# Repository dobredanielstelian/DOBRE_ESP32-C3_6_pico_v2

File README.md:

# DOBRE_ESP32-C3_6_pico_v2
ESP32-C3 evaluation board with e-ink display and multiple sensors

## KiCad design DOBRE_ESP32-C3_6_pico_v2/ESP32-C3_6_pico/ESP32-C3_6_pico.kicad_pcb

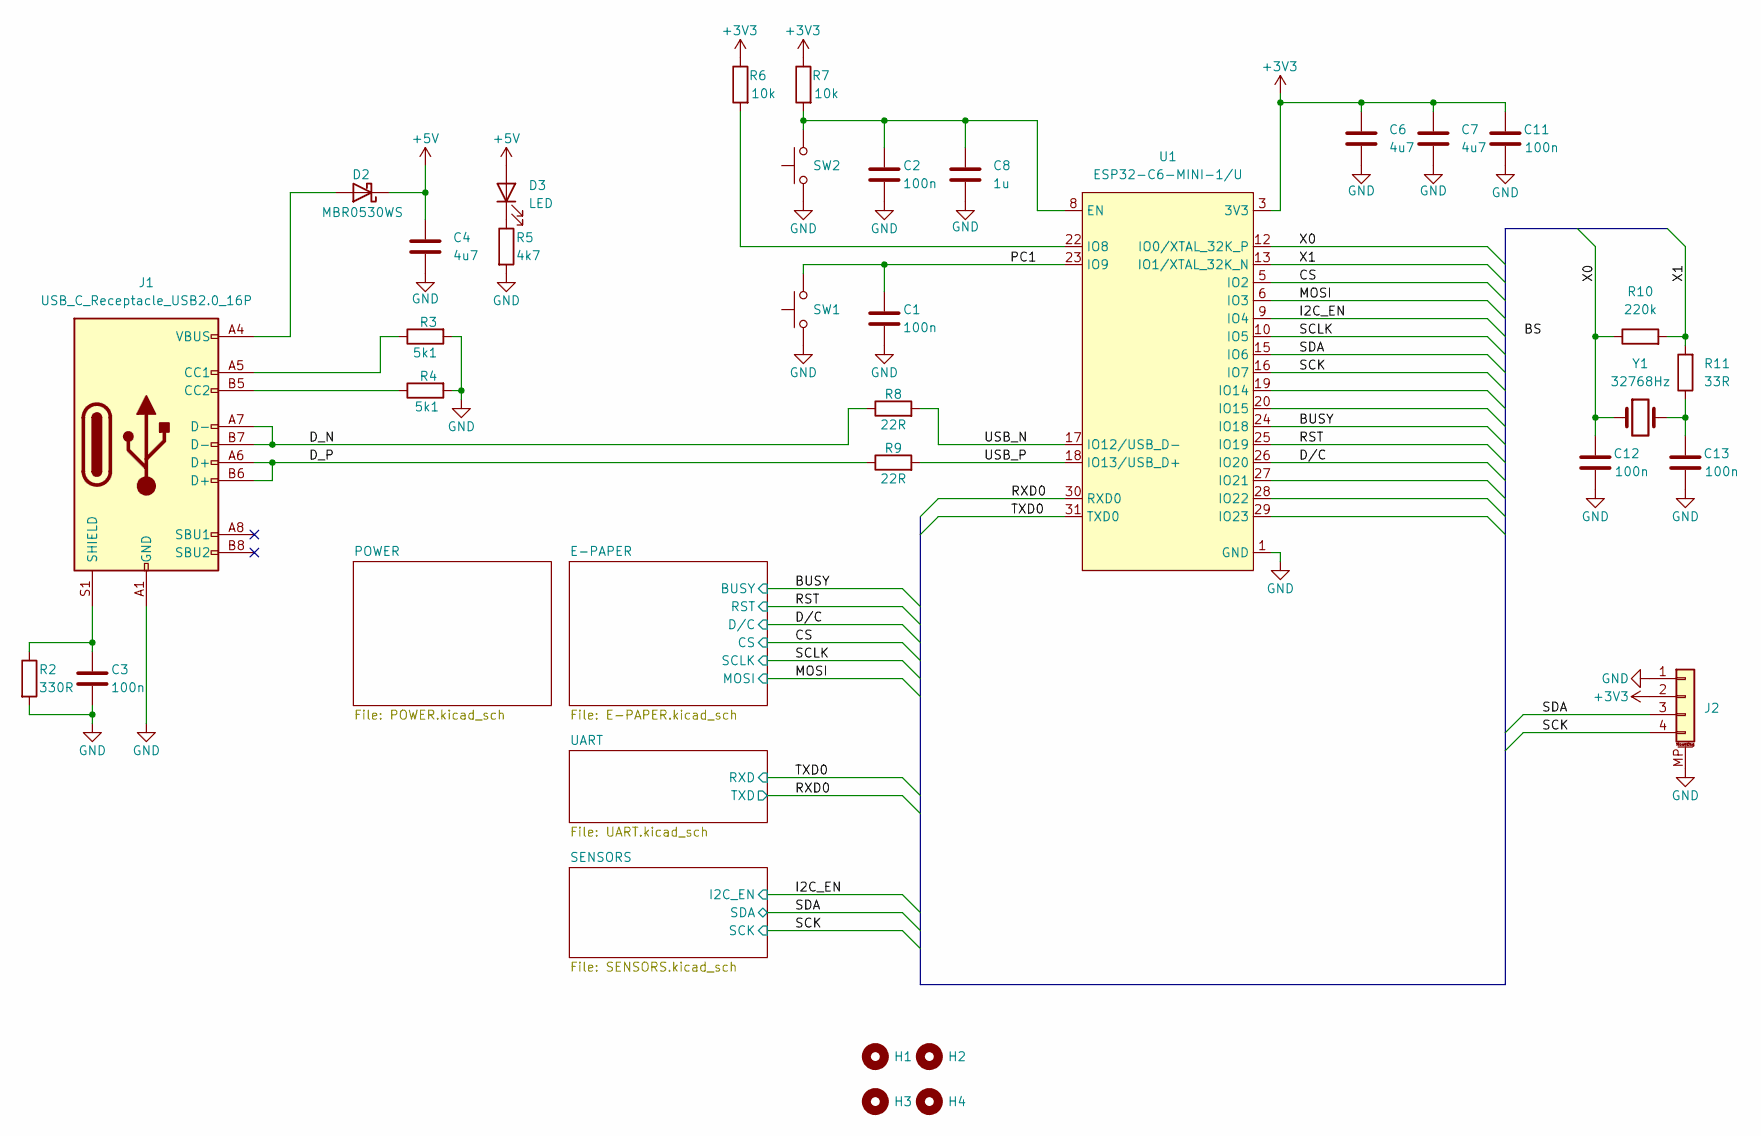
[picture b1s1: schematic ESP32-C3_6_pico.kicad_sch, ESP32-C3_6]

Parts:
C1, C2, C3, C11, C12, C13: 100n; C_0402_1005Metric
C4, C6, C7: 4u7; C_0402_1005Metric
C8: 1u; C_0402_1005Metric
D2: MBR0530WS; D_SOD-323
D3: LED; D_0402_1005Metric
H1, H2, H3, H4: MountingHole_3.2mm_M3
J1: USB_C_Receptacle_USB2.0_16P; USB_C_Receptacle_Palconn_UTC16-G
J2: Conn_01x04_MountingPin; JST_SH_SM04B-SRSS-TB_1x04-1MP_P1.00mm_Horizontal
R2: 330R; R_0402_1005Metric
R3, R4: 5k1; R_0402_1005Metric
R5: 4k7; R_0402_1005Metric
R6, R7: 10k; R_0402_1005Metric
R8, R9: 22R; R_0402_1005Metric
R10: 220k; R_0402_1005Metric
R11: 33R; R_0402_1005Metric
SW1, SW2: SW_Push; SW_Push_SPST_NO_Alps_SKRK
U1: ESP32-C6-MINI-1/U; ESP32-C6-MINI-1
Y1: 32768Hz; Crystal_SMD_2012-2Pin_2.0x1.2mm

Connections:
+3V3: C6.1, C7.1, C11.1, J2.2, R6.1, R7.1, U1.3 (3V3); also elsewhere on the board
+5V: C4.1, D2.1 (K), D3.2 (A); also elsewhere on the board
/BUSY: U1.24 (IO18); also elsewhere on the board
/CS: U1.5 (IO2); also elsewhere on the board
/D_N: J1.A7 (D-), J1.B7 (D-), R8.1
/D_P: J1.A6 (D+), J1.B6 (D+), R9.1
/D/C: U1.26 (IO20); also elsewhere on the board
/I2C_EN: U1.9 (IO4); also elsewhere on the board
/MOSI: U1.6 (IO3); also elsewhere on the board
/PC1: C1.1, SW1.2, U1.23 (IO9)
/RST: U1.25 (IO19); also elsewhere on the board
/RXD0: U1.30 (RXD0); also elsewhere on the board
/SCK: J2.4, U1.16 (IO7); also elsewhere on the board
/SCLK: U1.10 (IO5); also elsewhere on the board
/SDA: J2.3, U1.15 (IO6); also elsewhere on the board
/TXD0: U1.31 (TXD0); also elsewhere on the board
/USB_N: R8.2, U1.17 (IO12/USB_D-)
/USB_P: R9.2, U1.18 (IO13/USB_D+)
/X0: C12.1, R10.1, U1.12 (IO0/XTAL_32K_P), Y1.1
/X1: R10.2, R11.2, U1.13 (IO1/XTAL_32K_N)
GND: C1.2, C2.2, C3.2, C4.2, C6.2, C7.2, C8.2, C11.2, C12.2, C13.2, J1.A1 (GND), J1.A12 (GND), J1.B1 (GND), J1.B12 (GND), J2.1, J2.MP (MountPin), R2.2, R3.2, R4.2, R5.2, SW1.1, SW2.1, U1.1 (GND), U1.2 (GND), U1.11 (GND), U1.14 (GND), U1.36 (GND), U1.37 (GND), U1.38 (GND), U1.39 (GND), U1.40 (GND), U1.41 (GND), U1.42 (GND), U1.43 (GND), U1.44 (GND), U1.45 (GND), U1.46 (GND), U1.47 (GND), U1.48 (GND), U1.49 (GND), U1.50 (GND), U1.51 (GND), U1.52 (GND), U1.53 (GND); also elsewhere on the board
unnamed: C13.1, R11.1, Y1.2
unnamed: D2.2 (A), J1.A4 (VBUS), J1.A9 (VBUS), J1.B4 (VBUS), J1.B9 (VBUS)
unnamed: D3.1 (K), R5.1
unnamed: J1.A5 (CC1), R3.1
unnamed: J1.B5 (CC2), R4.1
unnamed: C3.1, J1.S1 (SHIELD), R2.1
unnamed: C2.1, C8.1, R7.2, SW2.2, U1.8 (EN)
unnamed: R6.2, U1.22 (IO8)
unnamed: U1.4 (NC), U1.7 (NC), U1.21 (NC), U1.32 (NC), U1.33 (NC), U1.34 (NC), U1.35 (NC)

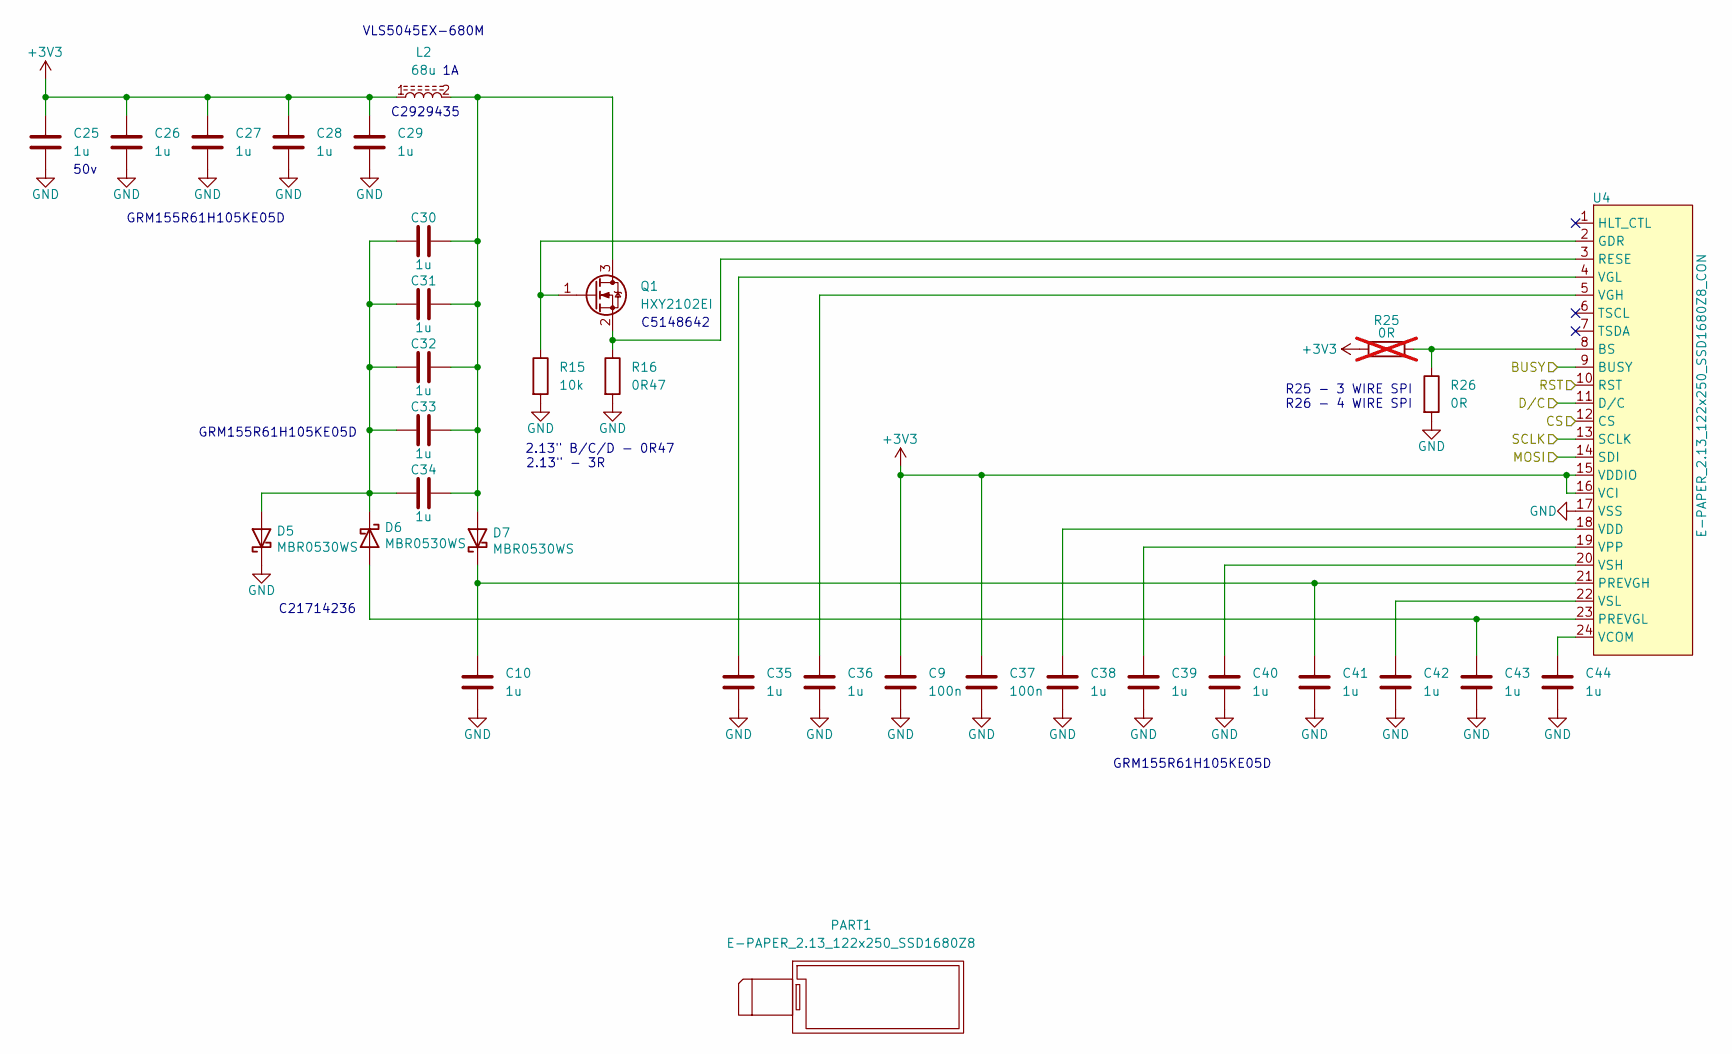
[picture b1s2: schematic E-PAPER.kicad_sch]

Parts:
C9, C37: 100n; C_0402_1005Metric
C10, C25, C26, C27, C28, C29, C30, C31, C32, C33, C34, C35, C36, C38, C39, C40, C41, C42, C43, C44: 1u; C_0402_1005Metric
D5, D6, D7: MBR0530WS; D_SOD-323
L2: 68u; Cx-54_inductor_C2929435
PART1: E-PAPER_2.13_122x250_SSD1680Z8
Q1: HXY2102EI; SOT-323_SC-70
R15: 10k; R_0402_1005Metric
R16: 0R47; R_0402_1005Metric
R25: 0R; R_0402_1005Metric; not fitted
R26: 0R; R_0402_1005Metric
U4: E-PAPER_2.13_122x250_SSD1680Z8_CON; TE_2-1734839-4_1x24-1MP_P0.5mm_Horizontal

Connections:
+3V3: C9.1, C25.1, C26.1, C27.1, C28.1, C29.1, C37.1, L2.1, R25.1, U4.15 (VDDIO), U4.16 (VCI); also elsewhere on the board
/BUSY: U4.9 (BUSY); also elsewhere on the board
/CS: U4.12 (CS); also elsewhere on the board
/D/C: U4.11 (D/C); also elsewhere on the board
/MOSI: U4.14 (SDI); also elsewhere on the board
/RST: U4.10 (RST); also elsewhere on the board
/SCLK: U4.13 (SCLK); also elsewhere on the board
GND: C9.2, C10.2, C25.2, C26.2, C27.2, C28.2, C29.2, C35.2, C36.2, C37.2, C38.2, C39.2, C40.2, C41.2, C42.2, C43.2, C44.2, D5.1 (K), R15.2, R16.2, R26.2, U4.17 (VSS), U4.MP; also elsewhere on the board
unnamed: C30.1, C31.1, C32.1, C33.1, C34.1, D5.2 (A), D6.1 (K)
unnamed: C43.1, D6.2 (A), U4.23 (PREVGL)
unnamed: C30.2, C31.2, C32.2, C33.2, C34.2, D7.2 (A), L2.2, Q1.3 (D)
unnamed: C10.1, C41.1, D7.1 (K), U4.21 (PREVGH)
unnamed: Q1.1 (G), R15.1, U4.2 (GDR)
unnamed: Q1.2 (S), R16.1, U4.3 (RESE)
unnamed: R25.2, R26.1, U4.8 (BS)
unnamed: C44.1, U4.24 (VCOM)
unnamed: C38.1, U4.18 (VDD)
unnamed: C36.1, U4.5 (VGH)
unnamed: C35.1, U4.4 (VGL)
unnamed: C39.1, U4.19 (VPP)
unnamed: C40.1, U4.20 (VSH)
unnamed: C42.1, U4.22 (VSL)

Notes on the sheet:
GRM155R61H105KE05D
C21714236
2.13" B/C/D - 0R47
C2929435
C5148642
R25 - 3 WIRE SPI R26 - 4 WIRE SPI
VLS5045EX-680M
50v
2.13" - 3R

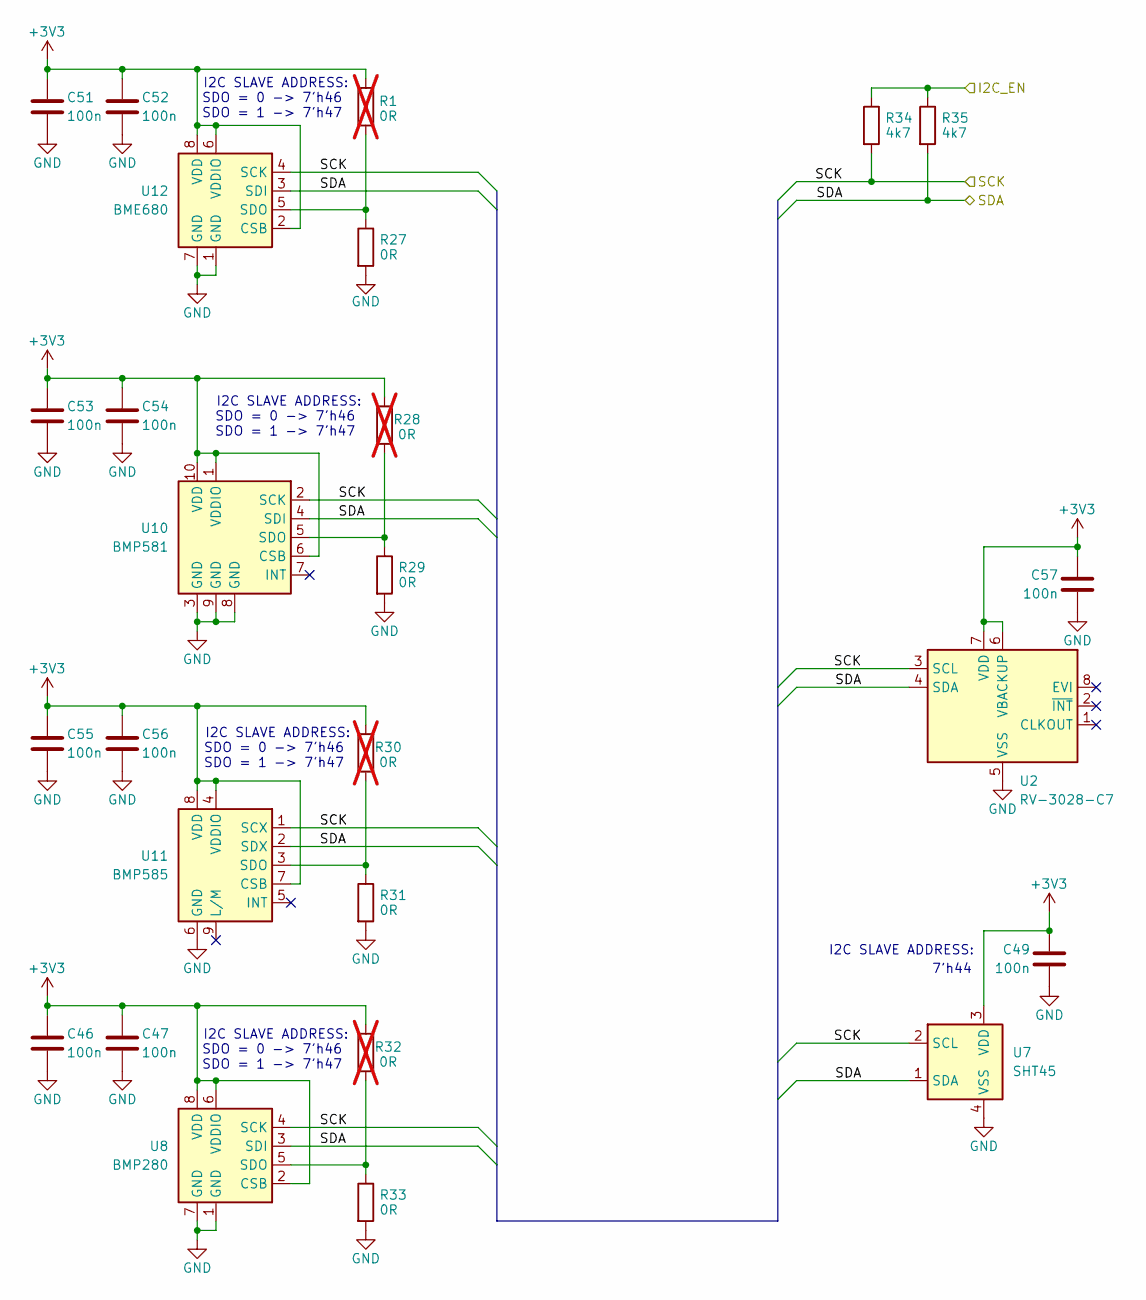
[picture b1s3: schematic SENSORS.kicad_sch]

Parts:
C46, C47, C49, C51, C52, C53, C54, C55, C56, C57: 100n; C_0402_1005Metric
R1, R28, R30, R32: 0R; R_0402_1005Metric; not fitted
R27, R29, R31, R33: 0R; R_0402_1005Metric
R34, R35: 4k7; R_0402_1005Metric
U2: RV-3028-C7
U7: SHT45; Sensirion_DFN-4_1.5x1.5mm_P0.8mm_SHT4x_NoCentralPad
U8: BMP280; Bosch_LGA-8_2x2.5mm_P0.65mm_ClockwisePinNumbering
U10: BMP581
U11: BMP585
U12: BME680; Bosch_LGA-8_3x3mm_P0.8mm_ClockwisePinNumbering

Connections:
+3V3: C46.1, C47.1, C49.1, C51.1, C52.1, C53.1, C54.1, C55.1, C56.1, C57.1, R1.2, R28.2, R30.2, R32.2, U2.6 (VBACKUP), U2.7 (VDD), U7.3 (VDD), U8.2 (CSB), U8.6 (VDDIO), U8.8 (VDD), U10.1 (VDDIO), U10.6 (CSB), U10.10 (VDD), U11.4 (VDDIO), U11.7 (CSB), U11.8 (VDD), U12.2 (CSB), U12.6 (VDDIO), U12.8 (VDD); also elsewhere on the board
/I2C_EN: R34.1, R35.1; also elsewhere on the board
/SCK: R34.2, U2.3 (SCL), U7.2 (SCL), U8.4 (SCK), U10.2 (SCK), U11.1 (SCX), U12.4 (SCK); also elsewhere on the board
/SDA: R35.2, U2.4 (SDA), U7.1 (SDA), U8.3 (SDI), U10.4 (SDI), U11.2 (SDX), U12.3 (SDI); also elsewhere on the board
GND: C46.2, C47.2, C49.2, C51.2, C52.2, C53.2, C54.2, C55.2, C56.2, C57.2, R27.2, R29.2, R31.2, R33.2, U2.5 (VSS), U7.4 (VSS), U8.1 (GND), U8.7 (GND), U10.3 (GND), U10.8 (GND), U10.9 (GND), U11.6 (GND), U12.1 (GND), U12.7 (GND); also elsewhere on the board
unnamed: R32.1, R33.1, U8.5 (SDO)
unnamed: R28.1, R29.1, U10.5 (SDO)
unnamed: R30.1, R31.1, U11.3 (SDO)
unnamed: R1.1, R27.1, U12.5 (SDO)

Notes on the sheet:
7'h44
SDO = 0 -> 7'h46 SDO = 1 -> 7'h47
I2C SLAVE ADDRESS:

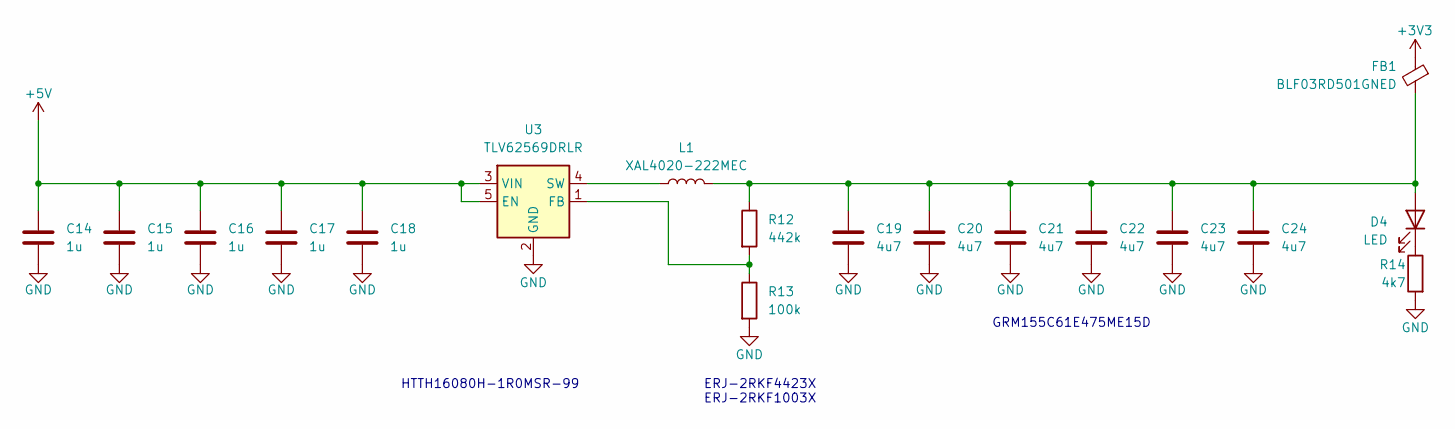
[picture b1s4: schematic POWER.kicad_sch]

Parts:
C14, C15, C16, C17, C18: 1u; C_0402_1005Metric
C19, C20, C21, C22, C23, C24: 4u7; C_0402_1005Metric
D4: LED; D_0402_1005Metric
FB1: BLF03RD501GNED; L_0402_1005Metric
L1: XAL4020-222MEC; L_Coilcraft_XxL4040
R12: 442k; R_0402_1005Metric
R13: 100k; R_0402_1005Metric
R14: 4k7; R_0402_1005Metric
U3: TLV62569DRLR; SOT-563

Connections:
+3V3: FB1.1; also elsewhere on the board
+5V: C14.1, C15.1, C16.1, C17.1, C18.1, U3.3 (VIN), U3.5 (EN); also elsewhere on the board
GND: C14.2, C15.2, C16.2, C17.2, C18.2, C19.2, C20.2, C21.2, C22.2, C23.2, C24.2, R13.2, R14.2, U3.2 (GND); also elsewhere on the board
unnamed: C19.1, C20.1, C21.1, C22.1, C23.1, C24.1, D4.2 (A), FB1.2, L1.2, R12.1
unnamed: D4.1 (K), R14.1
unnamed: R12.2, R13.1, U3.1 (FB)
unnamed: L1.1, U3.4 (SW)

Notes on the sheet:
GRM155C61E475ME15D
ERJ-2RKF4423X
ERJ-2RKF1003X
HTTH16080H-1R0MSR-99

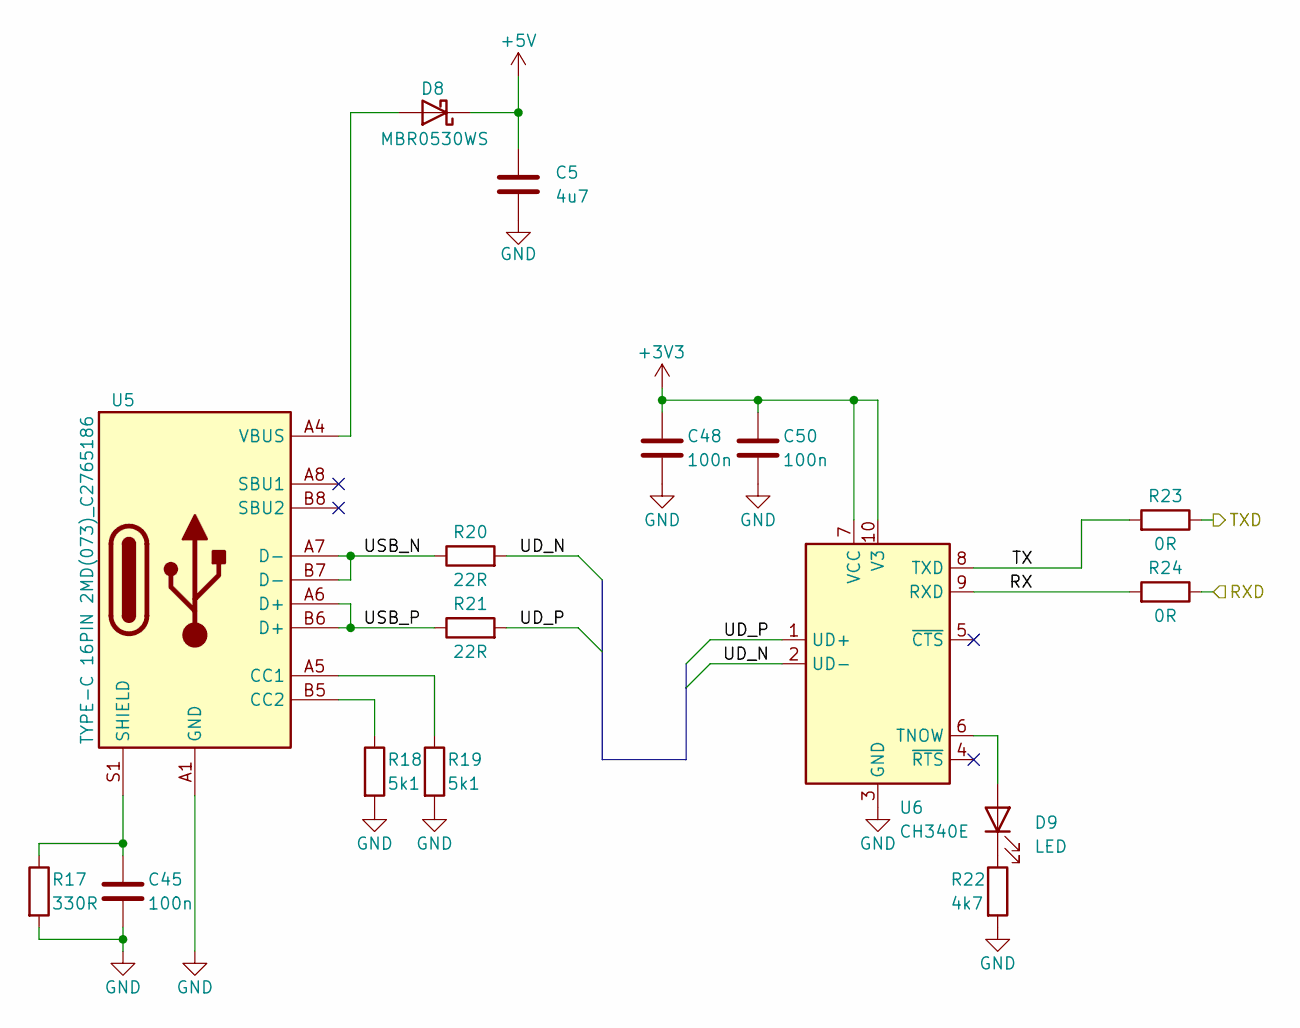
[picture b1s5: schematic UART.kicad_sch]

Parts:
C5: 4u7; C_0402_1005Metric
C45, C48, C50: 100n; C_0402_1005Metric
D8: MBR0530WS; D_SOD-323
D9: LED; D_0402_1005Metric
R17: 330R; R_0402_1005Metric
R18, R19: 5k1; R_0402_1005Metric
R20, R21: 22R; R_0402_1005Metric
R22: 4k7; R_0402_1005Metric
R23, R24: 0R; R_0402_1005Metric
U5: TYPE-C 16PIN 2MD(073)_C2765186; USB_C_Receptacle_Palconn_UTC16-G
U6: CH340E; MSOP-10_3x3mm_P0.5mm

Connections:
+3V3: C48.1, C50.1, U6.7 (VCC), U6.10 (V3); also elsewhere on the board
+5V: C5.1, D8.1 (K); also elsewhere on the board
/RXD0: R23.1; also elsewhere on the board
/TXD0: R24.1; also elsewhere on the board
/UART/RX: R24.2, U6.9 (RXD)
/UART/TX: R23.2, U6.8 (TXD)
/UART/UD_N: R20.2, U6.2 (UD-)
/UART/UD_P: R21.2, U6.1 (UD+)
/UART/USB_N: R20.1, U5.A7 (D-), U5.B7 (D-)
/UART/USB_P: R21.1, U5.A6 (D+), U5.B6 (D+)
GND: C5.2, C45.2, C48.2, C50.2, R17.2, R18.2, R19.2, R22.2, U5.A1 (GND), U5.A12 (GND), U5.B1 (GND), U5.B12 (GND), U6.3 (GND); also elsewhere on the board
unnamed: D8.2 (A), U5.A4 (VBUS), U5.A9 (VBUS), U5.B4 (VBUS), U5.B9 (VBUS)
unnamed: D9.2 (A), U6.6 (TNOW)
unnamed: D9.1 (K), R22.1
unnamed: R19.1, U5.A5 (CC1)
unnamed: R18.1, U5.B5 (CC2)
unnamed: C45.1, R17.1, U5.S1 (SHIELD)

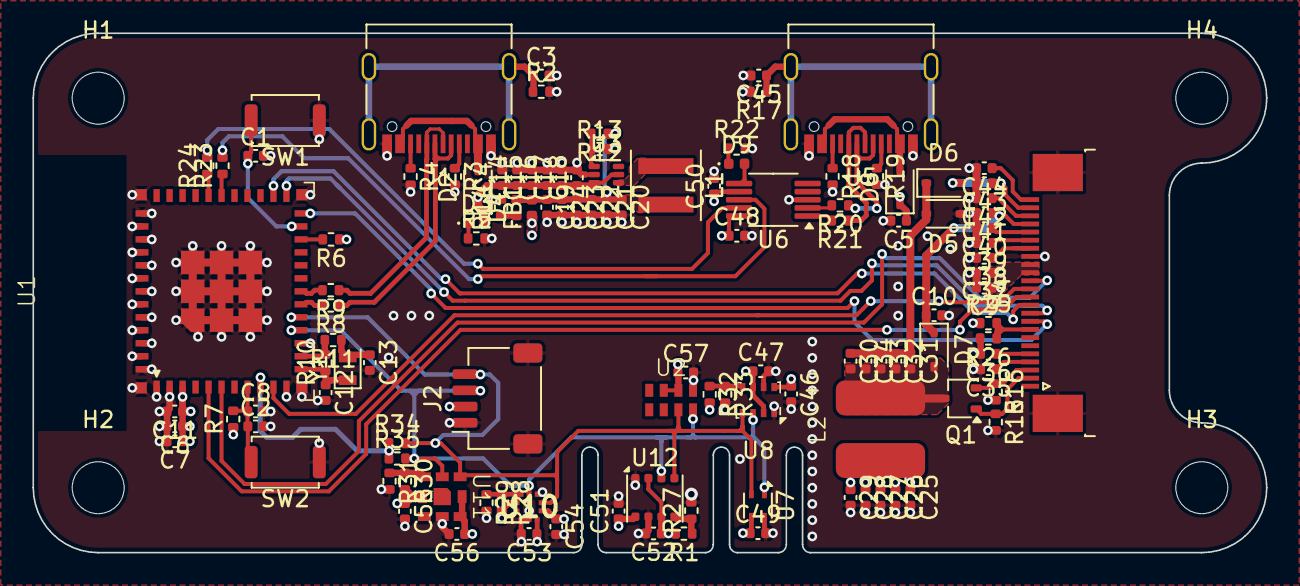
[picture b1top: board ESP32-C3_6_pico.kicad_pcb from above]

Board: 4 copper layers, 76.0 x 32.0 mm, 125 parts (1 on the bottom side), 64 nets.

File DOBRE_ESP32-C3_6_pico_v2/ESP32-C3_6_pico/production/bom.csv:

Designator,Footprint,Quantity,Value,LCSC Part #
"C1, C11, C12, C13, C2, C3, C37, C45, C46, C47, C48, C49, C50, C51, C52, C53, C54, C55, C56, C57, C9",0402,21,100n,
"C10, C14, C15, C16, C17, C18, C25, C26, C27, C28, C29, C30, C31, C32, C33, C34, C35, C36, C38, C39, C40, C41, C42, C43, C44, C8",0402,26,1u,
"C19, C20, C21, C22, C23, C24, C4, C5, C6, C7",0402,10,4u7,
"D2, D5, D6, D7, D8",D_SOD-323,5,MBR0530WS,
"D3, D4, D9",0402,3,LED,
FB1,0402,1,BLF03RD501GNED,
J1,USB_C_Receptacle_Palconn_UTC16-G,1,USB_C_Receptacle_USB2.0_16P,
J2,JST_SH_SM04B-SRSS-TB_1x04-1MP_P1.00mm_Horizontal,1,Conn_01x04_MountingPin,
L1,L_Coilcraft_XxL4040,1,XAL4020-222MEC,
L2,Cx-54_inductor_C2929435,1,68u,
Q1,SOT-323_SC-70,1,HXY2102EI,
"R1, R23, R24, R25, R26, R27, R28, R29, R30, R31, R32, R33",0402,12,0R,
R10,0402,1,220k,
R11,0402,1,33R,
R12,0402,1,442k,
R13,0402,1,100k,
"R14, R22, R34, R35, R5",0402,5,4k7,
"R15, R6, R7",0402,3,10k,
R16,0402,1,0R47,
"R17, R2",0402,2,330R,
"R18, R19, R3, R4",0402,4,5k1,
"R20, R21, R8, R9",0402,4,22R,
"SW1, SW2",SW_Push_SPST_NO_Alps_SKRK,2,SW_Push,
U1,ESP32-C6-MINI-1,1,ESP32-C6-MINI-1/U,
U10,BMP581,1,BMP581,
U11,BMP585,1,BMP585,
U12,Bosch_LGA-8_3x3mm_P0.8mm_ClockwisePinNumbering,1,BME680,
U2,RV-3028-C7,1,RV-3028-C7,
U3,SOT-563,1,TLV62569DRLR,
U4,TE_2-1734839-4_1x24-1MP_P0.5mm_Horizontal,1,E-PAPER_2.13_122x250_SSD1680Z8_CON,
U5,USB_C_Receptacle_Palconn_UTC16-G,1,TYPE-C 16PIN 2MD(073)_C2765186,
U6,MSOP-10_3x3mm_P0.5mm,1,CH340E,
U7,Sensirion_DFN-4_1.5x1.5mm_P0.8mm_SHT4x_NoCentralPad,1,SHT45,
U8,Bosch_LGA-8_2x2.5mm_P0.65mm_ClockwisePinNumbering,1,BMP280,
Y1,Crystal_SMD_2012-2Pin_2.0x1.2mm,1,32768Hz,

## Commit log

2024-12-20 Add the Kicad project to Git
2024-12-20 Add images forlder
2024-12-20 Add picture
